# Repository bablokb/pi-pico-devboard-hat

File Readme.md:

Pi-Pico-Devboard-Hat
====================

This repository contains the KiCAD project files of a Pico development hat.

The hat connects power, UART0 and the debug-port of the pico to the
respective pins of the Pi. You will also find a number of buttons, LEDs,
an I2C-connector with pullups (controlled by jumpers), and an SPI-connector.

The design uses only through-hole components, so soldering should be easy.
The Pico is soldered directly to the hat, thanks to the castellated holes
this is no major problem. Just watch out that you don't accidently fill
the holes if you also want to attach headers directly to the Pico (which
you most certainly want to do).

Schematic
---------

Layout
------

License
-------

Shield: [![CC BY-SA 4.0][cc-by-sa-shield]][cc-by-sa]

This work is licensed under a
[Creative Commons Attribution-ShareAlike 4.0 International
License][cc-by-sa].

[![CC BY-SA 4.0][cc-by-sa-image]][cc-by-sa]

[cc-by-sa]: http://creativecommons.org/licenses/by-sa/4.0/
[cc-by-sa-image]: https://licensebuttons.net/l/by-sa/4.0/88x31.png
[cc-by-sa-shield]:
https://img.shields.io/badge/License-CC%20BY--SA%204.0-lightgrey.svg

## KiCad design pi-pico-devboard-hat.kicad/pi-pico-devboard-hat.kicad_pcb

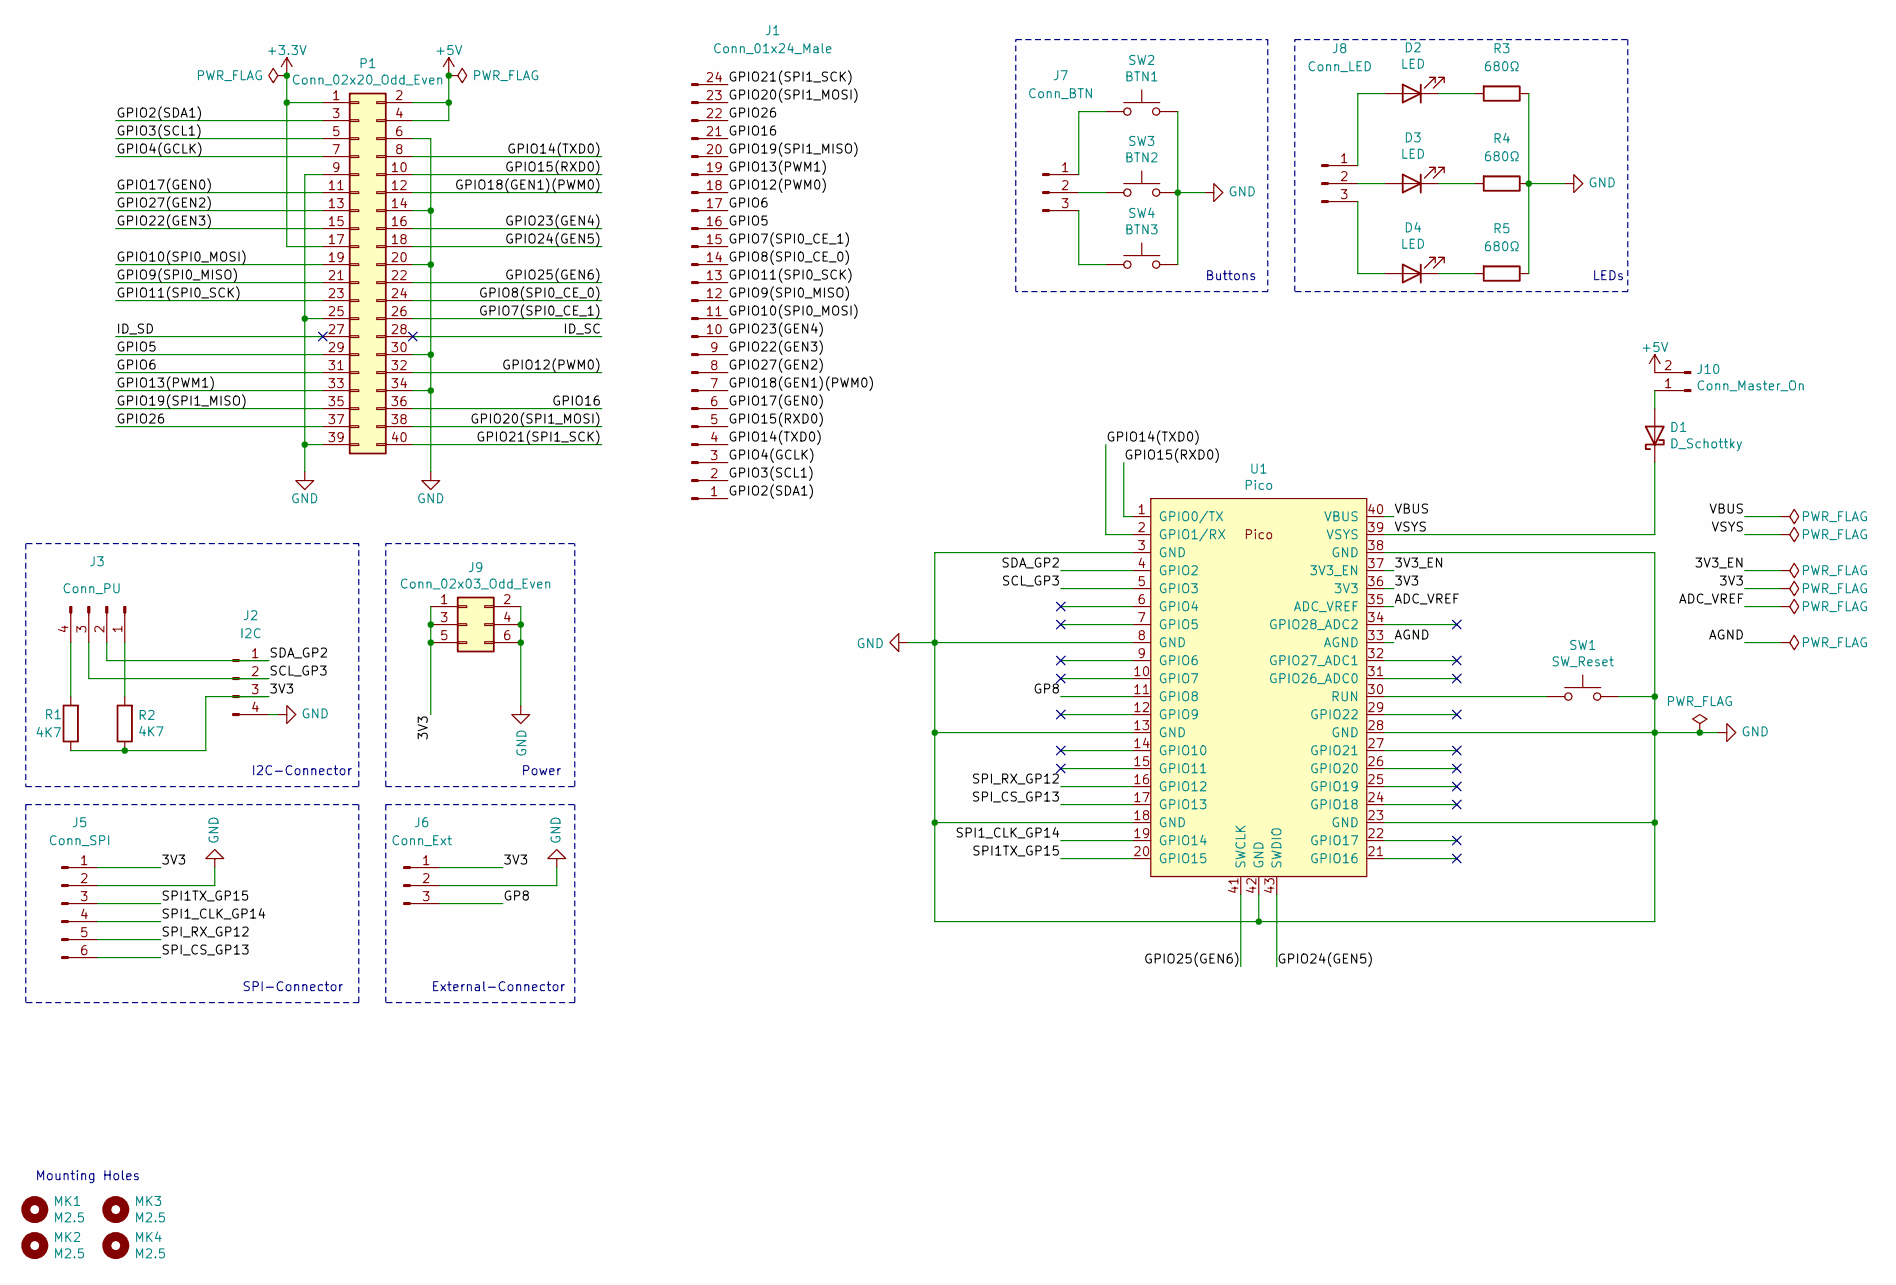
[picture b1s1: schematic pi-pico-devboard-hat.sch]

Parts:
D1: D_Schottky; D_DO-41_SOD81_P7.62mm_Horizontal
D2, D3, D4: LED; LED_D3.0mm
J1: Conn_01x24_Male; PinHeader_1x24_P2.54mm_Vertical
J2: I2C; PinHeader_1x04_P2.54mm_Vertical
J3: Conn_PU; PinHeader_1x04_P2.54mm_Vertical
J5: Conn_SPI; PinHeader_1x06_P2.54mm_Vertical
J6: Conn_Ext; PinHeader_1x03_P2.54mm_Vertical
J7: Conn_BTN; PinHeader_1x03_P2.54mm_Vertical
J8: Conn_LED; PinHeader_1x03_P2.54mm_Vertical
J9: Conn_02x03_Odd_Even; PinHeader_2x03_P2.54mm_Vertical
J10: Conn_Master_On; PinHeader_1x02_P2.54mm_Vertical
MK1, MK2, MK3, MK4: M2.5; MountingHole_2.7mm_M2.5
P1: Conn_02x20_Odd_Even; PinSocket_2x20_P2.54mm_Vertical
R1, R2: 4K7; R_Axial_DIN0204_L3.6mm_D1.6mm_P5.08mm_Horizontal
R3, R4, R5: 680Ω; R_Axial_DIN0204_L3.6mm_D1.6mm_P5.08mm_Horizontal
SW1: SW_Reset; SW_PUSH_6mm
SW2: BTN1; SW_PUSH_SLIM_1x4
SW3: BTN2; SW_PUSH_SLIM_1x4
SW4: BTN3; SW_PUSH_SLIM_1x4
U1: Pico; RPi_Pico_SMD_TH

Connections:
+3V3: P1.1, P1.17
+5V: J10.2, P1.2, P1.4
/3V3: J2.3, J5.1, J6.1, J9.1, J9.3, J9.5, R1.1, R2.1, U1.36 (3V3)
/3V3_EN: U1.37 (3V3_EN)
/ADC_VREF: U1.35 (ADC_VREF)
/AGND: U1.33 (AGND)
/GP8: J6.3, U1.11 (GPIO8)
/GPIO2(SDA1): J1.1, P1.3
/GPIO3(SCL1): J1.2, P1.5
/GPIO4(GCLK): J1.3, P1.7
/GPIO5: J1.16, P1.29
/GPIO6: J1.17, P1.31
/GPIO7(SPI0_CE_1): J1.15, P1.26
/GPIO8(SPI0_CE_0): J1.14, P1.24
/GPIO9(SPI0_MISO): J1.12, P1.21
/GPIO10(SPI0_MOSI): J1.11, P1.19
/GPIO11(SPI0_SCK): J1.13, P1.23
/GPIO12(PWM0): J1.18, P1.32
/GPIO13(PWM1): J1.19, P1.33
/GPIO14(TXD0): J1.4, P1.8, U1.2 (GPIO1/RX)
/GPIO15(RXD0): J1.5, P1.10, U1.1 (GPIO0/TX)
/GPIO16: J1.21, P1.36
/GPIO17(GEN0): J1.6, P1.11
/GPIO18(GEN1)(PWM0): J1.7, P1.12
/GPIO19(SPI1_MISO): J1.20, P1.35
/GPIO20(SPI1_MOSI): J1.23, P1.38
/GPIO21(SPI1_SCK): J1.24, P1.40
/GPIO22(GEN3): J1.9, P1.15
/GPIO23(GEN4): J1.10, P1.16
/GPIO24(GEN5): P1.18, U1.43 (SWDIO)
/GPIO25(GEN6): P1.22, U1.41 (SWCLK)
/GPIO26: J1.22, P1.37
/GPIO27(GEN2): J1.8, P1.13
/ID_SC: P1.28
/ID_SD: P1.27
/SCL_GP3: J2.2, J3.3, U1.5 (GPIO3)
/SDA_GP2: J2.1, J3.2, U1.4 (GPIO2)
/SPI1TX_GP15: J5.3, U1.20 (GPIO15)
/SPI1_CLK_GP14: J5.4, U1.19 (GPIO14)
/SPI_CS_GP13: J5.6, U1.17 (GPIO13)
/SPI_RX_GP12: J5.5, U1.16 (GPIO12)
/VBUS: U1.40 (VBUS)
/VSYS: D1.1 (K), U1.39 (VSYS)
GND: J2.4, J5.2, J6.2, J9.2, J9.4, J9.6, P1.6, P1.9, P1.14, P1.20, P1.25, P1.30, P1.34, P1.39, R3.1, R4.1, R5.1, SW1.2, SW2.2, SW3.2, SW4.2, U1.3 (GND), U1.8 (GND), U1.13 (GND), U1.18 (GND), U1.23 (GND), U1.28 (GND), U1.38 (GND), U1.42 (GND)
unnamed: D1.2 (A), J10.1
unnamed: D2.1 (K), R3.2
unnamed: D2.2 (A), J8.1
unnamed: D3.1 (K), R4.2
unnamed: D3.2 (A), J8.2
unnamed: D4.1 (K), R5.2
unnamed: D4.2 (A), J8.3
unnamed: J3.1, R2.2
unnamed: J3.4, R1.2
unnamed: J7.1, SW2.1
unnamed: J7.2, SW3.1
unnamed: J7.3, SW4.1
unnamed: SW1.1, U1.30 (RUN)

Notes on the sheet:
Mounting Holes
I2C-Connector
SPI-Connector
External-Connector
Buttons
LEDs
Power

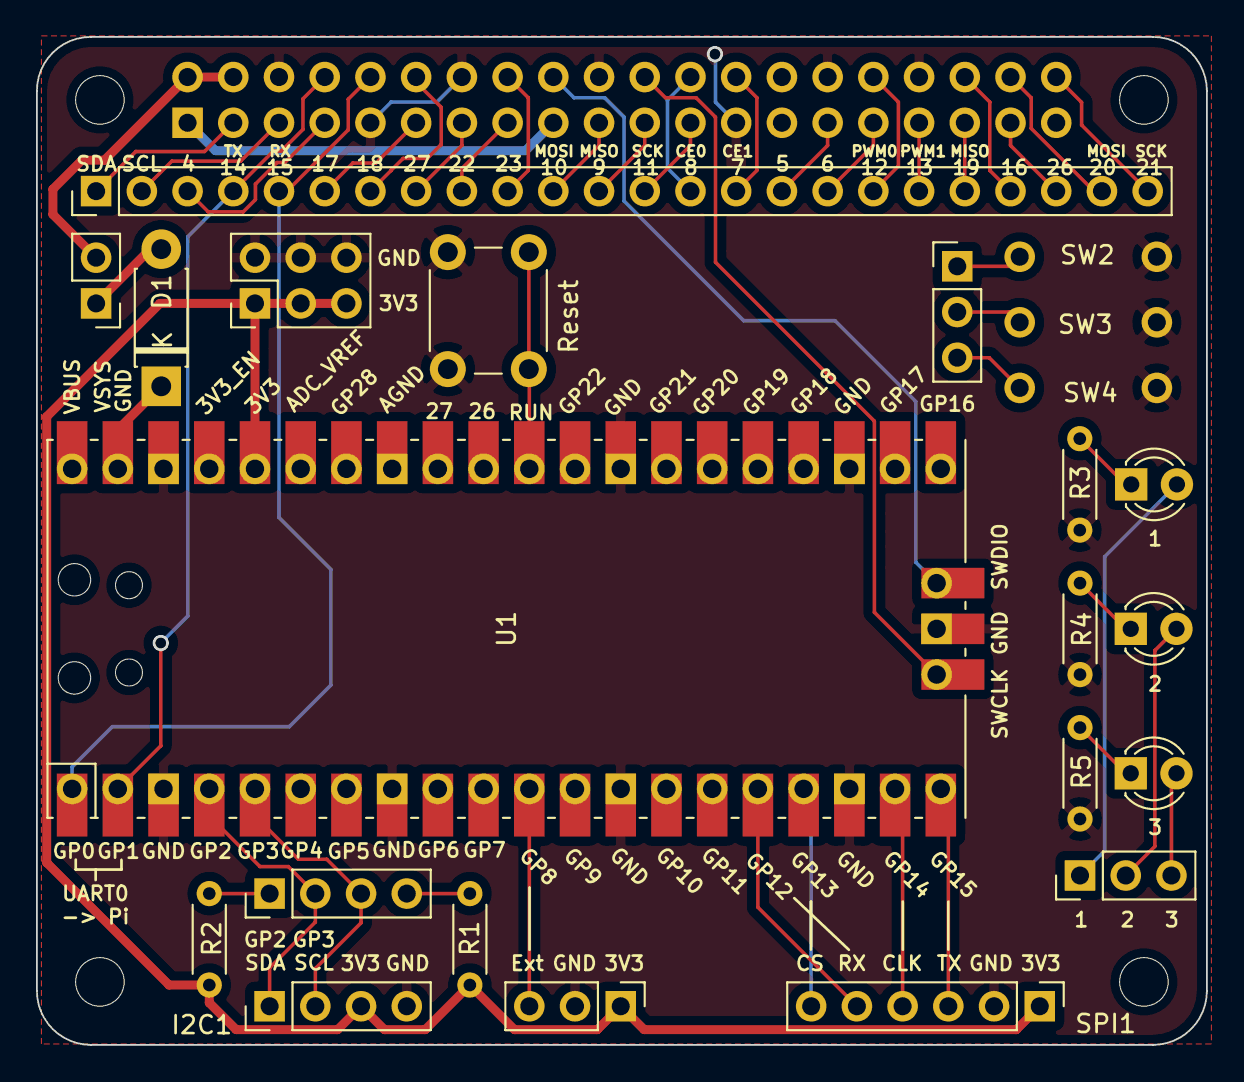
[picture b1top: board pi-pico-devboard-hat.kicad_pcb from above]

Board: 2 copper layers, 65.0 x 56.0 mm, 28 parts (1 on the bottom side), 51 nets.

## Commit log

2021-03-16 added footprints
2021-03-16 updated footprint for pico
2021-03-18 first prototype DRC error free
2021-03-18 Rev 2: removed unneeded connectors
2021-03-20 Rev 3: added IC-connector with optional pullups
2021-03-22 Rev 4: added SPI1-connector
2021-03-23 Rev 5: added external connector
2021-03-23 Rev 6: added buttons
2021-03-23 Rev 7: added LEDs
2021-03-23 Rev 8: added power-connector / fine-tuning
2021-03-27 Rev 9: added master power-jumper
2021-03-27 Rev 9.1: changed trace for 3V3
2021-03-27 Rev 10: reorg of I2C-pullup connector
2021-03-27 Rev 11: connect Pi-pins GPIO16/GPIO26 to pin-connector (remove GPIO24/GPIO25 used for SWD)
2021-03-27 fixed labels of Pi-pin-connector
2021-03-27 updated images
2021-04-17 fixed footprint and position of SW2-SW4
2021-05-23 fixed filename of 3D-image
2021-10-31 added section about license
